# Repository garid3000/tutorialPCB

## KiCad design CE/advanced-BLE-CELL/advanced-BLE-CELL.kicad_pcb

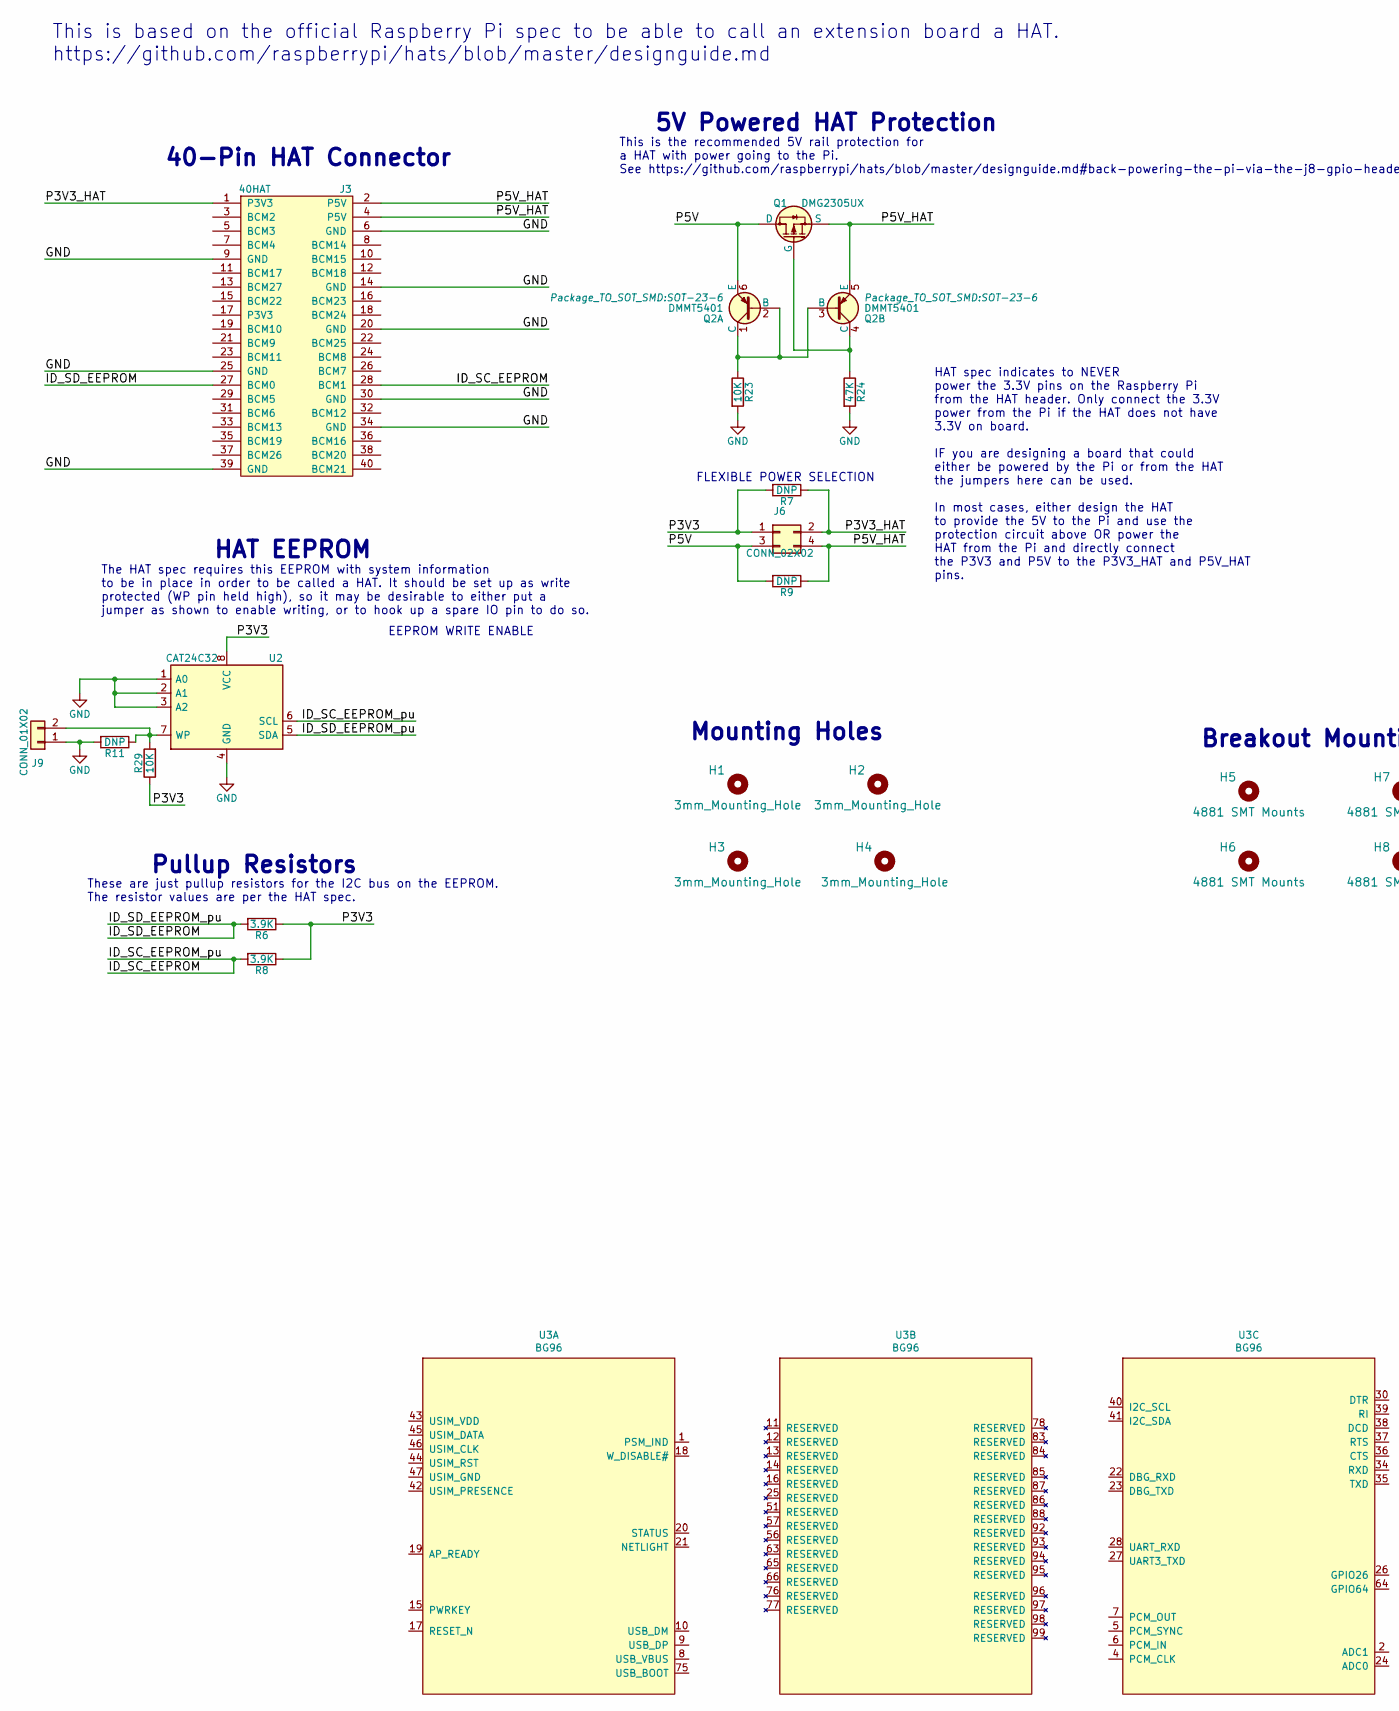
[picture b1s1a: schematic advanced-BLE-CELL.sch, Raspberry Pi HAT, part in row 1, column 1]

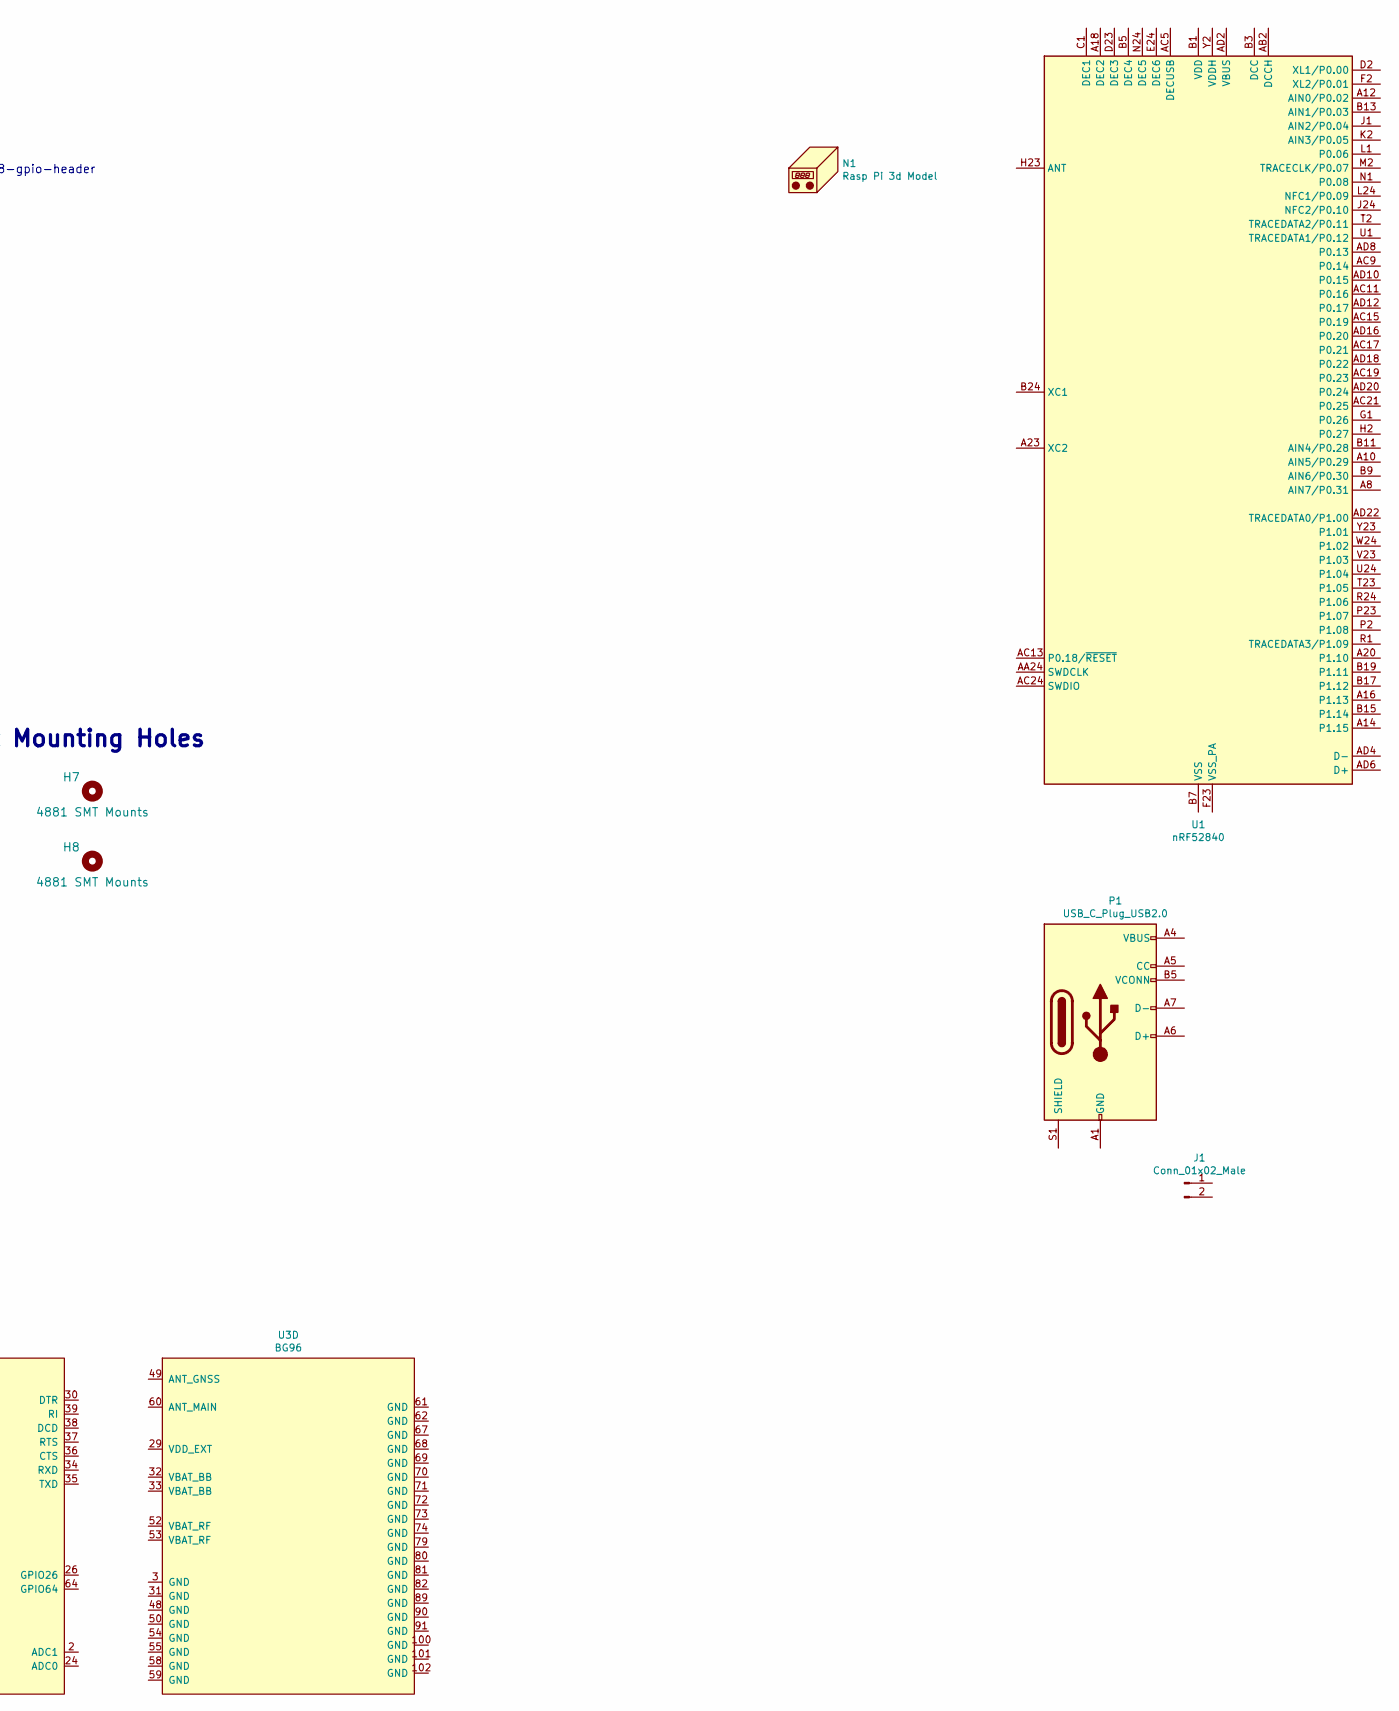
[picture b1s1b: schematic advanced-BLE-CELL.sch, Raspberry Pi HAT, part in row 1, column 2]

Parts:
H1, H2, H3, H4: 3mm_Mounting_Hole; NPTH_3mm_ID
H5, H6, H7, H8: 4881 SMT Mounts; 4881-Top
J1: Conn_01x02_Male; JST_PH_S2B-PH-SM4-TB_1x02-1MP_P2.00mm_Horizontal
J3: 40HAT; PinSocket_2x20_P2.54mm_Vertical-CENTER
J6: CONN_02X02; PinHeader_2x02_P2.54mm_Vertical
J9: CONN_01X02; PinHeader_1x02_P2.54mm_Vertical
N1: Rasp Pi 3d Model; KiCad-Logo_5mm_SilkScreen-rpi-module
P1: USB_C_Plug_USB2.0; USB_C_Receptacle_Palconn_UTC16-G
Q1: DMG2305UX; SOT-23
Q2: DMMT5401; SOT-23-6
R6, R8: 3.9K; R_0603_1608Metric_Pad0.84x1.00mm_HandSolder
R7, R9, R11: DNP; R_0603_1608Metric_Pad0.84x1.00mm_HandSolder
R23, R29: 10K; R_0603_1608Metric_Pad0.84x1.00mm_HandSolder
R24: 47K; R_0603_1608Metric_Pad0.84x1.00mm_HandSolder
U1: nRF52840; Nordic_AQFN-73-1EP_7x7mm_P0.5mm
U2: CAT24C32; SOIC-8_3.9x4.9mm_P1.27mm
U3: BG96

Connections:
/ID_SC_EEPROM: J3.28 (BCM1), R8.2, U2.6 (SCL)
/ID_SD_EEPROM: J3.27 (BCM0), R6.2, U2.5 (SDA)
/P3V3: J6.1, R6.1, R7.2, R8.1, R29.1, U2.8 (VCC)
/P3V3_HAT: J3.1 (P3V3), J6.2, R7.1
/P5V: J6.3, Q1.3 (D), Q2.6 (E), R9.2
/P5V_HAT: J3.2 (P5V), J3.4 (P5V), J6.4, Q1.2 (S), Q2.5 (E), R9.1
GND: J3.6 (GND), J3.9 (GND), J3.14 (GND), J3.20 (GND), J3.25 (GND), J3.30 (GND), J3.34 (GND), J3.39 (GND), J9.1, R11.2, R23.2, R24.2, U2.1 (A0), U2.2 (A1), U2.3 (A2), U2.4 (GND)
unnamed: J9.2, R11.1, R29.2, U2.7 (WP)
unnamed: P1.A1 (GND), P1.A12 (GND), P1.B1 (GND), P1.B12 (GND)
unnamed: P1.A4 (VBUS), P1.A9 (VBUS), P1.B4 (VBUS), P1.B9 (VBUS)
unnamed: Q1.1 (G), Q2.4 (C), R24.1
unnamed: Q2.1 (C), Q2.2 (B), Q2.3 (B), R23.1
unnamed: U1.A22 (VDD), U1.AD14 (VDD), U1.AD23 (VDD), U1.B1 (VDD), U1.W1 (VDD)
unnamed: U1.B7 (VSS), U1.EP (VSS)

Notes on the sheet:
FLEXIBLE POWER SELECTION
5V Powered HAT Protection
This is the recommended 5V rail protection for a HAT with power going to the Pi. See https://github.com/raspberrypi/hats/blob/master/designguide.md#back-powering-the-pi-via-the-j8-gpio-header
EEPROM WRITE ENABLE
Pullup Resistors
HAT EEPROM
Mounting Holes
40-Pin HAT Connector
HAT spec indicates to NEVER power the 3.3V pins on the Raspberry Pi from the HAT header. Only connect the 3.3V power from the Pi if the HAT does not have 3.3V on board. IF you are designing a board that could either be powered by the Pi or from the HAT the jumpers here can be used. In most cases, e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
The HAT spec requires this EEPROM with system information to be in place in order to be called a HAT. It should be set up as write protected (WP pin held high), so it may be desirable to either put a jumper as shown to enable writing, or to hook up a spare IO pin to do so.
These are just pullup resistors for the I2C bus on the EEPROM. The resistor values are per the HAT spec.
This is based on the official Raspberry Pi spec to be able to call an extension board a HAT. https://github.com/raspberrypi/hats/blob/master/designguide.md
Breakout Mounting Holes

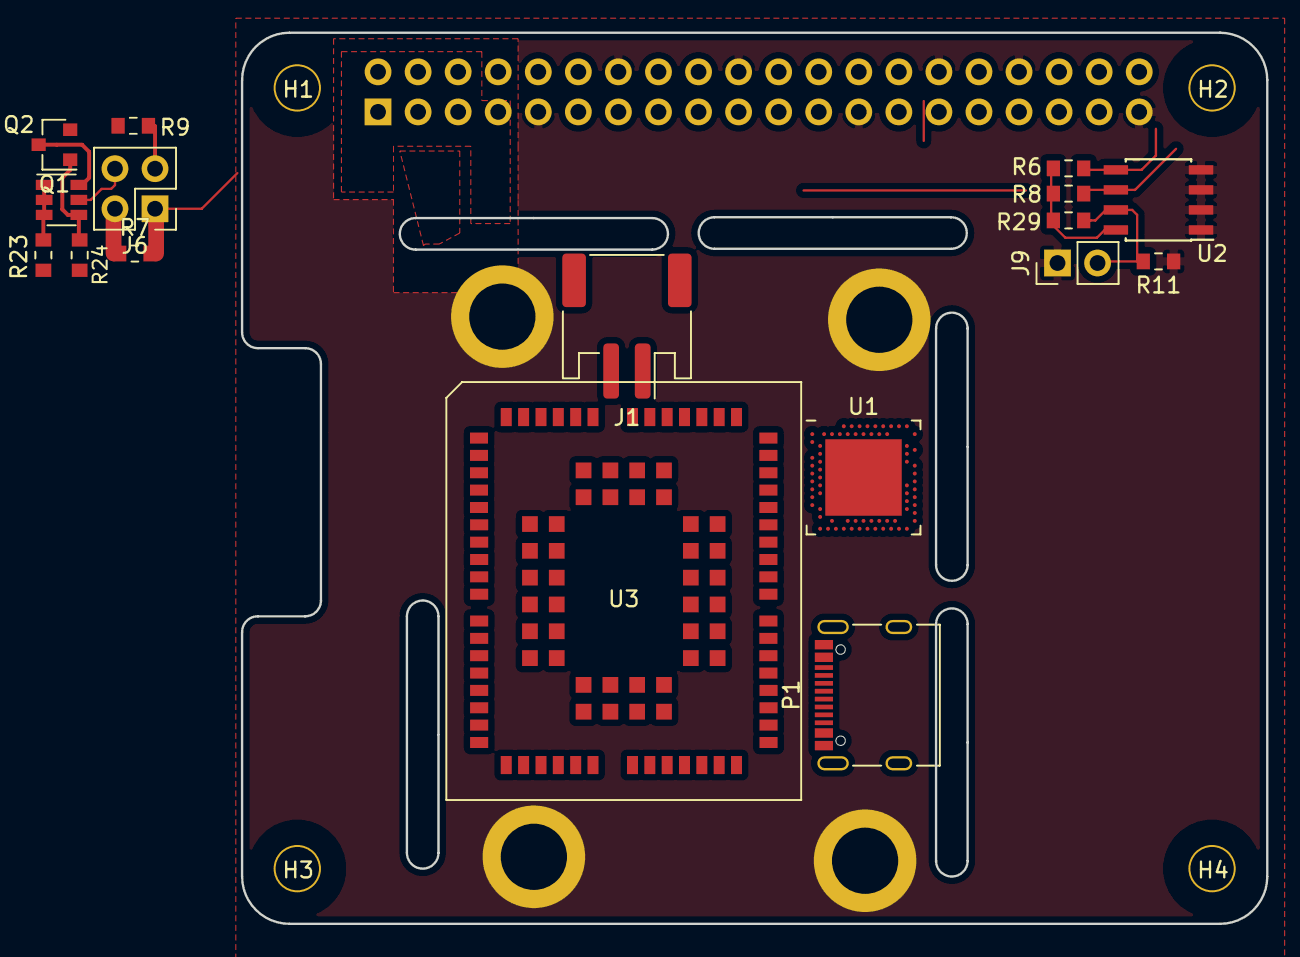
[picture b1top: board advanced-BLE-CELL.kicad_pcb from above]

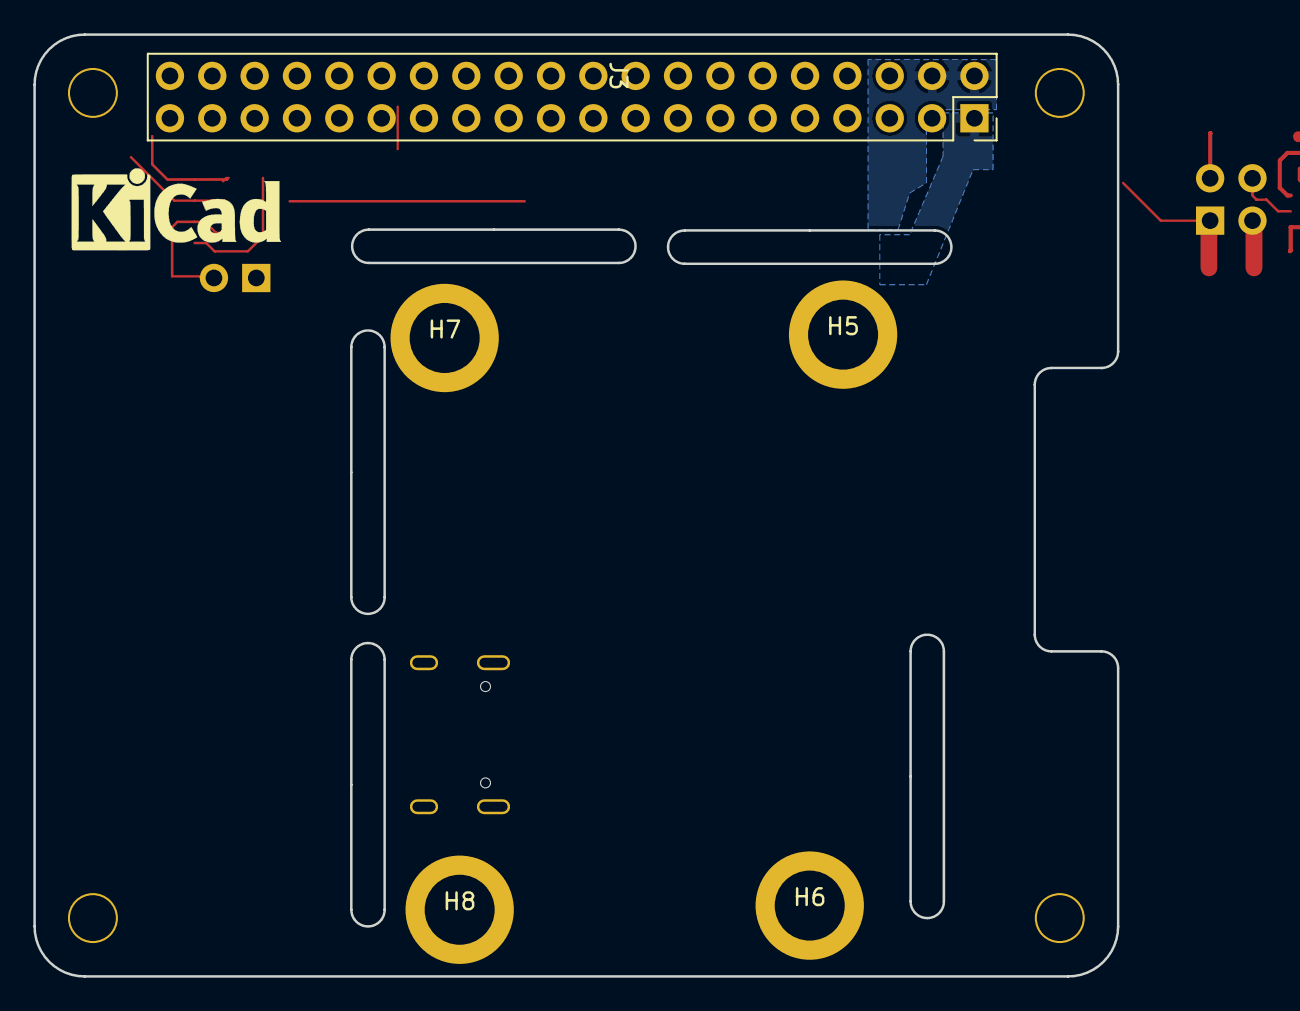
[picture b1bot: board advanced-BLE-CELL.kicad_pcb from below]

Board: 4 copper layers, 65.0 x 56.5 mm, 27 parts (6 on the bottom side), 14 nets.

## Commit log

2020-12-27 asdf
2020-12-28 updated 3d thing
2020-12-30 ASFd
